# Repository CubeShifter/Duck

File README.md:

# Duck
An rp2040 devboard that can be coded up to play a loud noise when pressed with a keyboard switch. The original goal for the project was to make it play a loud noise of your choice when you press the switch, but i wanted to make it more customizable so now its a pcb that you can do whatever with. sadly i did privitize my lapse links cause i put some pii in them so you will just have to trust my :hs:

Screenies!

Schematic

I foget what its called(Dont mind the drc errors i forgot to rerun it)

3d Model of top:

3d model of bottom:

# Steps for recreation:
Get the pcb fabricated, and solder on the componenets. I would highly reccomend PCBA, but you could also hand solder it. Once you build it, you can flash code on it like an rp2040 devboard. I want to see how people use the key and audio, so you should try using it somehow!

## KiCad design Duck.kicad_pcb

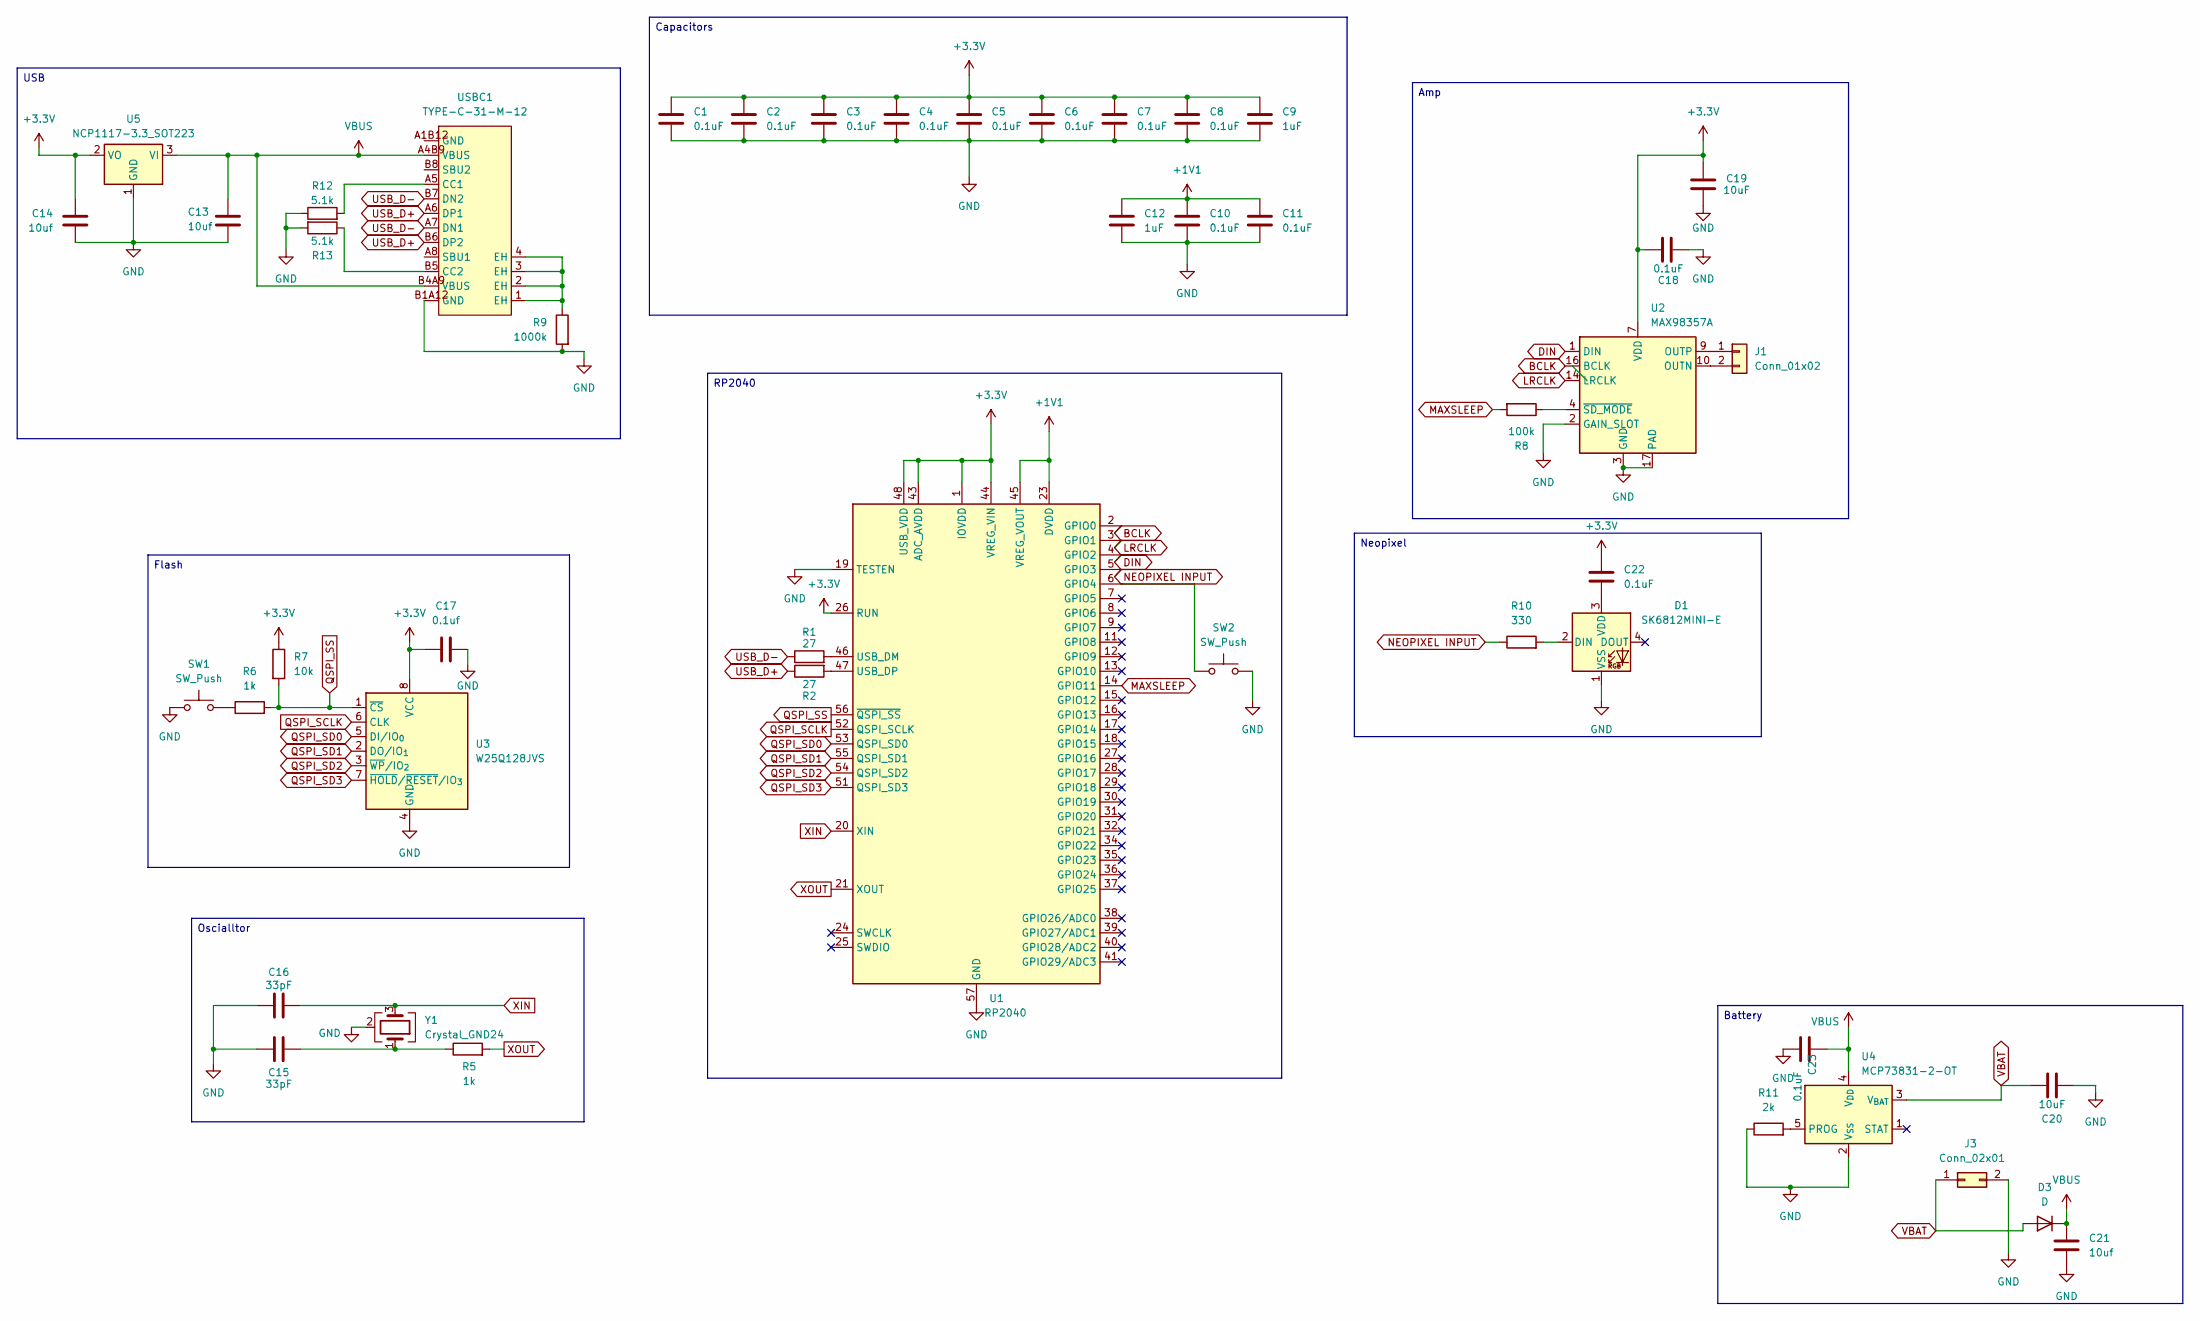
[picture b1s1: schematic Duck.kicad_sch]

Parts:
C1, C2, C3, C4, C5, C6, C7, C8, C10, C11, C18, C22, C23: 0.1uF; C_0402_1005Metric
C9, C12: 1uF; C_0402_1005Metric
C13, C14, C21: 10uf; C_0603_1608Metric
C15, C16: 33pF; C_0402_1005Metric
C17: 0.1uf; C_0402_1005Metric
C19, C20: 10uF; C_0603_1608Metric
D1: SK6812MINI-E; LED_SK6812MINI-E_3.2x2.8mm_P1.5mm_ReverseMount
D3: D; D_0402_1005Metric
J1: Conn_01x02; PinSocket_1x02_P2.54mm_Vertical
J3: Conn_02x01; PinSocket_1x02_P2.54mm_Vertical
R1, R2: 27; R_0402_1005Metric
R5, R6: 1k; R_0402_1005Metric
R7: 10k; R_0402_1005Metric
R8: 100k; R_0402_1005Metric
R9: 1000k; R_0402_1005Metric
R10: 330; R_0402_1005Metric
R11: 2k; R_0402_1005Metric
R12, R13: 5.1k; R_0402_1005Metric
SW1: SW_Push; SW-SMD_L3.9-W3.0-P4.45
SW2: SW_Push; SW_Cherry_MX_1.00u_PCB
U1: RP2040; QFN-56-1EP_7x7mm_P0.4mm_EP3.2x3.2mm
U2: MAX98357A; TQFN-16-1EP_3x3mm_P0.5mm_EP1.23x1.23mm
U3: W25Q128JVS; SOIC-8_5.3x5.3mm_P1.27mm
U4: MCP73831-2-OT; SOT-23-5
U5: NCP1117-3.3_SOT223; SOT-223-3_TabPin2
USBC1: TYPE-C-31-M-12; USB-C_SMD-TYPE-C-31-M-12_1; MPN TYPE-C-31-M-12; LCSC Part C165948
Y1: Crystal_GND24; CRYSTAL-SMD_4P-L3.2-W2.5-BL

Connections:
+1V1: C10.1, C11.1, C12.1, U1.23 (DVDD), U1.45 (VREG_VOUT), U1.50 (DVDD)
+3.3V: C1.1, C2.1, C3.1, C4.1, C5.1, C6.1, C7.1, C8.1, C9.1, C14.1, C17.1, C18.2, C19.2, C22.1, R7.1, U1.1 (IOVDD), U1.10 (IOVDD), U1.22 (IOVDD), U1.26 (RUN), U1.33 (IOVDD), U1.42 (IOVDD), U1.43 (ADC_AVDD), U1.44 (VREG_VIN), U1.48 (USB_VDD), U1.49 (IOVDD), U2.7 (VDD), U2.8 (VDD), U3.8 (VCC), U5.2 (VO)
A+: J1.1, U2.9 (OUTP)
A-: J1.2, U2.10 (OUTN)
BCLK: U1.2 (GPIO0), U2.16 (BCLK)
DIN: U1.4 (GPIO2), U2.1 (DIN)
GND: C1.2, C2.2, C3.2, C4.2, C5.2, C6.2, C7.2, C8.2, C9.2, C10.2, C11.2, C12.2, C13.2, C14.2, C15.1, C16.1, C17.2, C18.1, C19.1, C20.2, C21.2, C23.2, D1.1 (VSS), J3.2, R9.2, R11.1, R12.1, R13.2, SW1.1, SW2.2, U1.19 (TESTEN), U1.57 (GND), U2.2 (GAIN_SLOT), U2.3 (GND), U2.11 (GND), U2.15 (GND), U2.17 (PAD), U3.4 (GND), U4.2 (V_{SS}), U5.1 (GND), USBC1.A1B12 (GND), USBC1.B1A12 (GND), Y1.2 (G), Y1.4 (G)
LRCLK: U1.3 (GPIO1), U2.14 (LRCLK)
MAXSLEEP: R8.2, U1.14 (GPIO11)
NEOPIXEL INPUT: R10.1, U1.5 (GPIO3)
unnamed: C15.2, R5.1, Y1.1
unnamed: D1.2 (DIN), R10.2
unnamed: C22.2, D1.3 (VDD)
unnamed: R6.1, SW1.2
unnamed: R9.1, USBC1.1 (EH), USBC1.2 (EH), USBC1.3 (EH), USBC1.4 (EH)
unnamed: SW2.1, U1.6 (GPIO4)
unnamed: R1.2, U1.46 (USB_DM)
unnamed: R2.2, U1.47 (USB_DP)
unnamed: R8.1, U2.4 (~SD_MODE)
unnamed: R11.2, U4.5 (PROG)
unnamed: R12.2, USBC1.A5 (CC1)
unnamed: R13.1, USBC1.B5 (CC2)
QSPI_SCLK: U1.52 (QSPI_SCLK), U3.6 (CLK)
QSPI_SD0: U1.53 (QSPI_SD0), U3.5 (DI/IO_{0})
QSPI_SD1: U1.55 (QSPI_SD1), U3.2 (DO/IO_{1})
QSPI_SD2: U1.54 (QSPI_SD2), U3.3 (~WP/IO_{2})
QSPI_SD3: U1.51 (QSPI_SD3), U3.7 (~HOLD/~RESET/IO_{3})
QSPI_SS: R6.2, R7.2, U1.56 (~QSPI_SS), U3.1 (~CS)
USB_D+: R2.1, USBC1.A6 (DP1), USBC1.B6 (DP2)
USB_D-: R1.1, USBC1.A7 (DN1), USBC1.B7 (DN2)
VBAT: C20.1, D3.2 (A), J3.1, U4.3 (V_{BAT})
VBUS: C13.1, C21.1, C23.1, D3.1 (K), U4.4 (V_{DD}), U5.3 (VI), USBC1.A4B9 (VBUS), USBC1.B4A9 (VBUS)
XIN: C16.2, U1.20 (XIN), Y1.3
XOUT: R5.2, U1.21 (XOUT)

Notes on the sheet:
RP2040
Neopixel
Flash
USB
Amp
Capacitors
Battery
Oscialltor

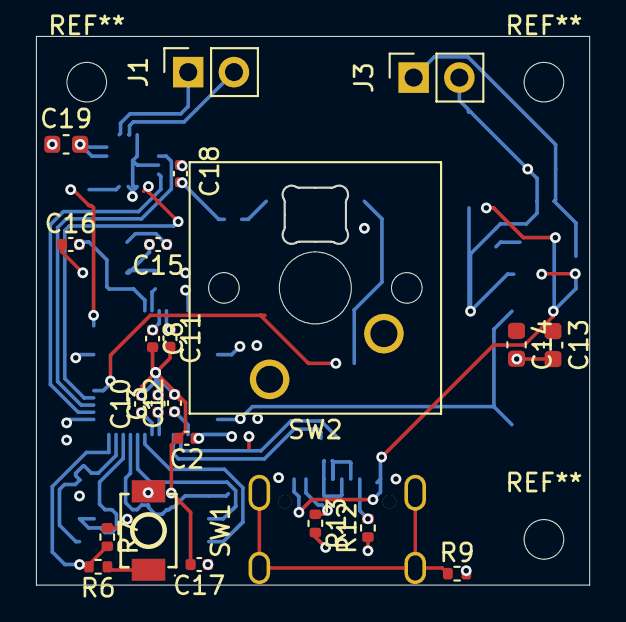
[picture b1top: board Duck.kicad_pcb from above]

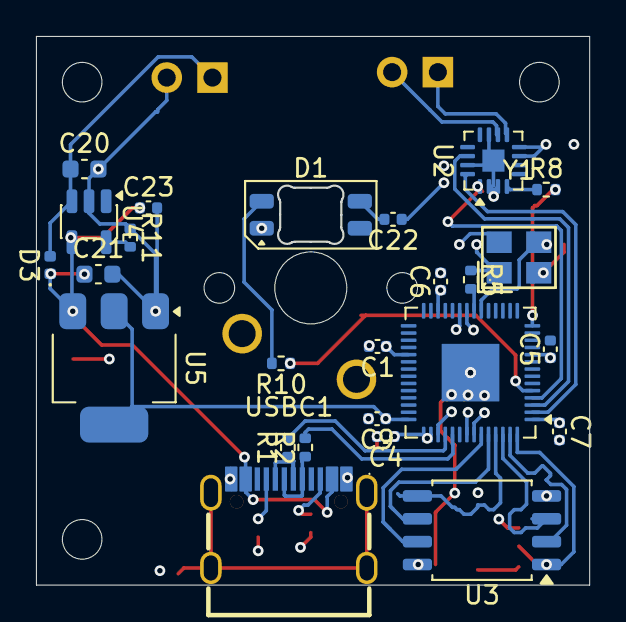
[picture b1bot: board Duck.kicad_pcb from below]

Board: 4 copper layers, 30.7 x 30.5 mm, 47 parts (25 on the bottom side), 34 nets.

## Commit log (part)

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2026-05-03 Add initial entry to JOURNAL.md
2026-05-03 Add metadata to JOURNAL.md
    Added metadata for journal entry including title, author, description, and creation date.
2026-05-06 Add new entry 'meow,moew' to BOM.csv
2026-05-06 Update BOM.csv header and format
2026-05-06 Add ID column and update BOM.csv format
2026-05-06 Add Mini Oval Speaker to BOM
2026-05-07 Add journal entry for June 8th on parts selection
    Documented parts selection and research for devboard project.
2026-05-07 Update JOURNAL.md with new images and time spent
    Added images and updated time spent on project.
2026-05-07 Remove price and store info for Mini Oval Speaker
    Removed the price and store information for the Mini Oval Speaker.
2026-05-08 Update JOURNAL.md with time spent and new entry
    Added total time spent and updated journal entry for May 6th.
2026-05-08 Add journal entry for May 7th on PCB design
    Documented progress on PCB design and learning KiCad.
2026-05-09 Update JOURNAL.md with May 8th activities
    Documented progress on USB, Oscillator, and Flash components.
2026-05-13 Update JOURNAL.md with May 9th-10th entries
    Documented progress on audio and battery research, including chip selection and schematic copying.
2026-05-25 Update JOURNAL.md with recent project progress
    Added detailed entries for May 18th to May 25th, documenting work on audio and charging circuits, schematic revisions, and footprint assignments.
2026-05-25 Update journal with total time spent
    Added total time spent entry for May 25th.
2026-05-26 All of the pcb stuff
    I kinda forgot to comit lol
2026-05-26 Hopefully this works
2026-05-31 I havent commited in a while but now it works good
2026-05-31 Document work on schematic layout for May 26th
    Added entry for May 26th detailing work on schematic layout and time spent.
2026-05-31 Update JOURNAL.md with recent project entries
    Added new entries for May 27th to 28th detailing schematic layout work and lipo selection.
